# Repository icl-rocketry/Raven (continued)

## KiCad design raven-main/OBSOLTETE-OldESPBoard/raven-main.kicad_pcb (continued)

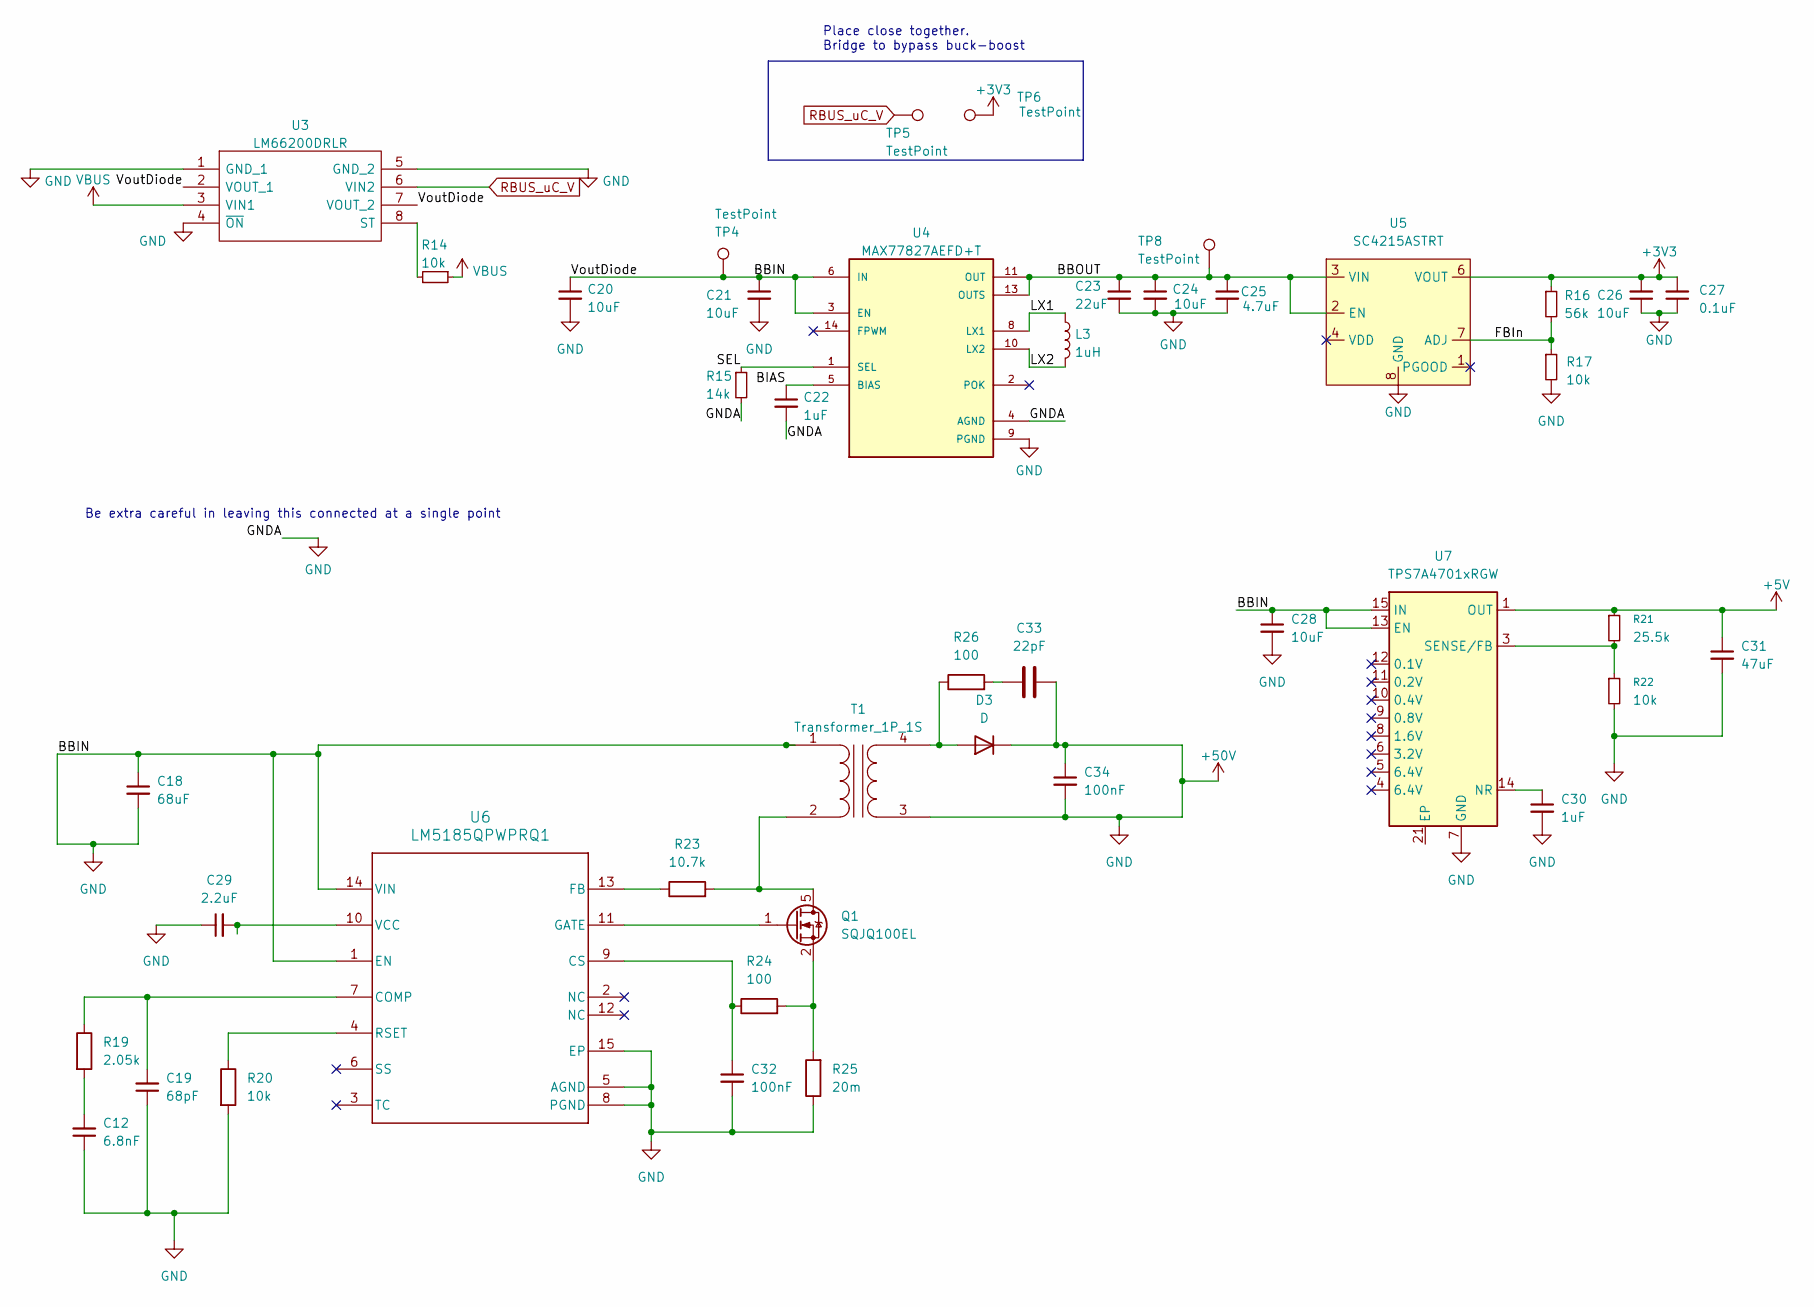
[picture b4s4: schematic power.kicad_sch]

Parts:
C12: 6.8nF; C_0402_1005Metric
C18: 68uF; C_0402_1005Metric
C19: 68pF; C_0402_1005Metric
C20, C24, C26, C28: 10uF; C_0402_1005Metric
C21: 10uF; C_0603_1608Metric
C22, C30: 1uF; C_0402_1005Metric
C23: 22uF; C_0603_1608Metric
C25: 4.7uF; C_0402_1005Metric
C27: 0.1uF; C_0402_1005Metric
C29: 2.2uF; C_0402_1005Metric
C31: 47uF; C_0402_1005Metric
C32, C34: 100nF; C_0402_1005Metric
C33: 22pF; C_0402_1005Metric
D3: D
L3: 1uH; L_0805_2012Metric
Q1: SQJQ100EL; LFPAK88
R14, R17, R20, R22: 10k; R_0402_1005Metric
R15: 14k; R_0402_1005Metric
R16: 56k; R_0402_1005Metric
R19: 2.05k; R_0402_1005Metric
R21: 25.5k; R_0402_1005Metric
R23: 10.7k; R_0402_1005Metric
R24, R26: 100; R_0402_1005Metric
R25: 20m; R_0402_1005Metric
T1: Transformer_1P_1S
TP4, TP5, TP6, TP8: TestPoint; TestPoint_Pad_D1.5mm
U3: LM66200DRLR; SOTFL50P160X60-8N; Manufacturer_Part_Number LM66200DRLR; Mouser Part Number 595-LM66200DRLR
U4: MAX77827AEFD+T; CONV_MAX77827AEFD+T; PARTREV B
U5: SC4215ASTRT; SOIC127P599X175-9N
U6: LM5185QPWPRQ1; PWP0014G-IPC_A
U7: TPS7A4701xRGW; Texas_RGW0020A_VQFN-20-1EP_5x5mm_P0.65mm_EP3.15x3.15mm_Ther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

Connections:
+3V3: C26.2, C27.2, R16.1, TP6.1 (1_1), U5.6 (VOUT); also elsewhere on the board
+5V: C31.1, R21.1, U7.1 (OUT), U7.20 (OUT); also elsewhere on the board
+50V: C12.1, C18.1, C18.2, C19.1, C20.1, C20.2, C21.1, C21.2, C22.2, C23.2, C24.2, C25.2, C26.1, C27.1, C28.1, C28.2, C29.1, C30.2, C31.2, C32.2, C33.2, C34.1, C34.2, D3.1 (K), R15.2, R17.2, R20.2, R22.2, R25.1, T1.1 (AA), T1.3 (SA), TP4.1 (1_1), U3.1 (GND_1), U3.2 (VOUT_1), U3.4 (~ON), U3.5 (GND_2), U3.7 (VOUT_2), U4.3 (EN), U4.4 (AGND), U4.6 (IN), U4.9 (PGND), U5.8 (GND), U5.9 (GND), U6.1 (EN), U6.5 (AGND), U6.8 (PGND), U6.14 (VIN), U6.15 (EP), U7.7 (GND), U7.13 (EN), U7.15 (IN), U7.16 (IN); also elsewhere on the board
/Power/BBOUT: C23.1, C24.1, C25.1, TP8.1 (1_1), U4.11 (OUT), U4.13 (OUTS), U5.2 (EN), U5.3 (VIN)
/Power/BIAS: C22.1, U4.5 (BIAS)
/Power/FBIn: R16.2, R17.1, U5.7 (ADJ)
/Power/LX1: L3.1, U4.8 (LX1)
/Power/LX2: L3.2, U4.10 (LX2)
/Power/SEL: R15.1, U4.1 (SEL)
unnamed: C12.2, R19.2
unnamed: C33.1, R26.2
unnamed: D3.2 (A), R26.1, T1.4 (SB)
unnamed: Q1.5 (D), R23.2, T1.2 (AB)
unnamed: Q1.1 (G), U6.11 (GATE)
unnamed: Q1.2 (S), Q1.3 (S), Q1.4 (S), R24.2, R25.2
unnamed: R14.2, U3.8 (ST)
unnamed: C19.2, R19.1, U6.7 (COMP)
unnamed: C32.1, R24.1, U6.9 (CS)
unnamed: R23.1, U6.13 (FB)
unnamed: R20.1, U6.4 (RSET)
unnamed: C29.2, U6.10 (VCC)
unnamed: C30.1, U7.14 (NR)
unnamed: R21.2, R22.1, U7.3 (SENSE/FB)
RBUS_uC_V: TP5.1 (1_1), U3.6 (VIN2); also elsewhere on the board
VBUS: R14.1, U3.3 (VIN1); also elsewhere on the board

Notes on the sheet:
Place close together. Bridge to bypass buck-boost
Be extra careful in leaving this connected at a single point

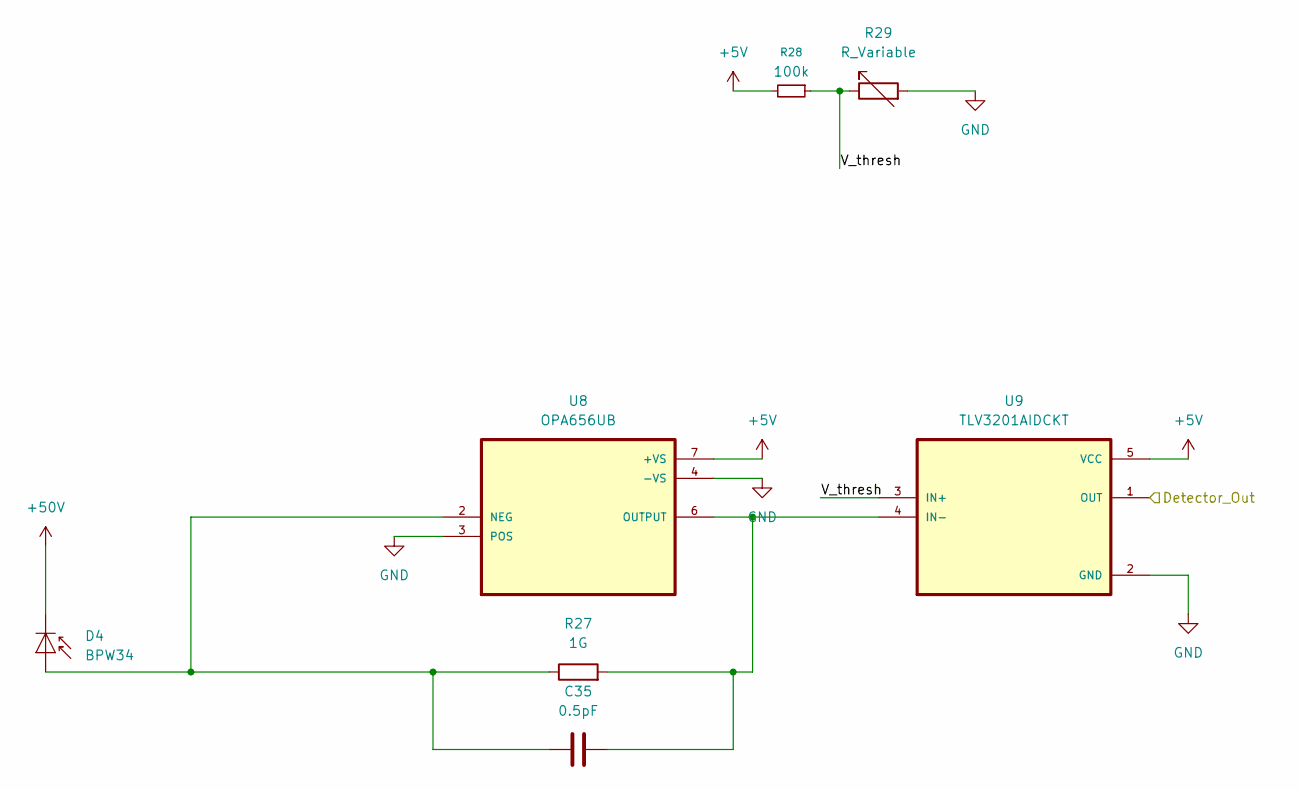
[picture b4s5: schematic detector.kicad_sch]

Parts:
C35: 0.5pF; C_0402_1005Metric
D4: BPW34; Osram_DIL2_4.3x4.65mm_P5.08mm
R27: 1G; R_0402_1005Metric
R28: 100k; R_0402_1005Metric
R29: R_Variable; R_0402_1005Metric
U8: OPA656UB; SOIC127P599X175-8N
U9: TLV3201AIDCKT; SOT65P210X110-5N

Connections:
+5V: R28.2, U8.7 (+VS), U9.5 (VCC); also elsewhere on the board
/detector/V_thresh_A: R28.1, R29.1, U9.3 (IN+)
unnamed: C35.1, D4.2 (A), R27.1, U8.2 (NEG)
unnamed: C35.2, R27.2, U8.6 (OUTPUT), U9.4 (IN-)
unnamed 49: R29.2, U8.3 (POS), U8.4 (-VS), U9.2 (GND); also elsewhere on the board

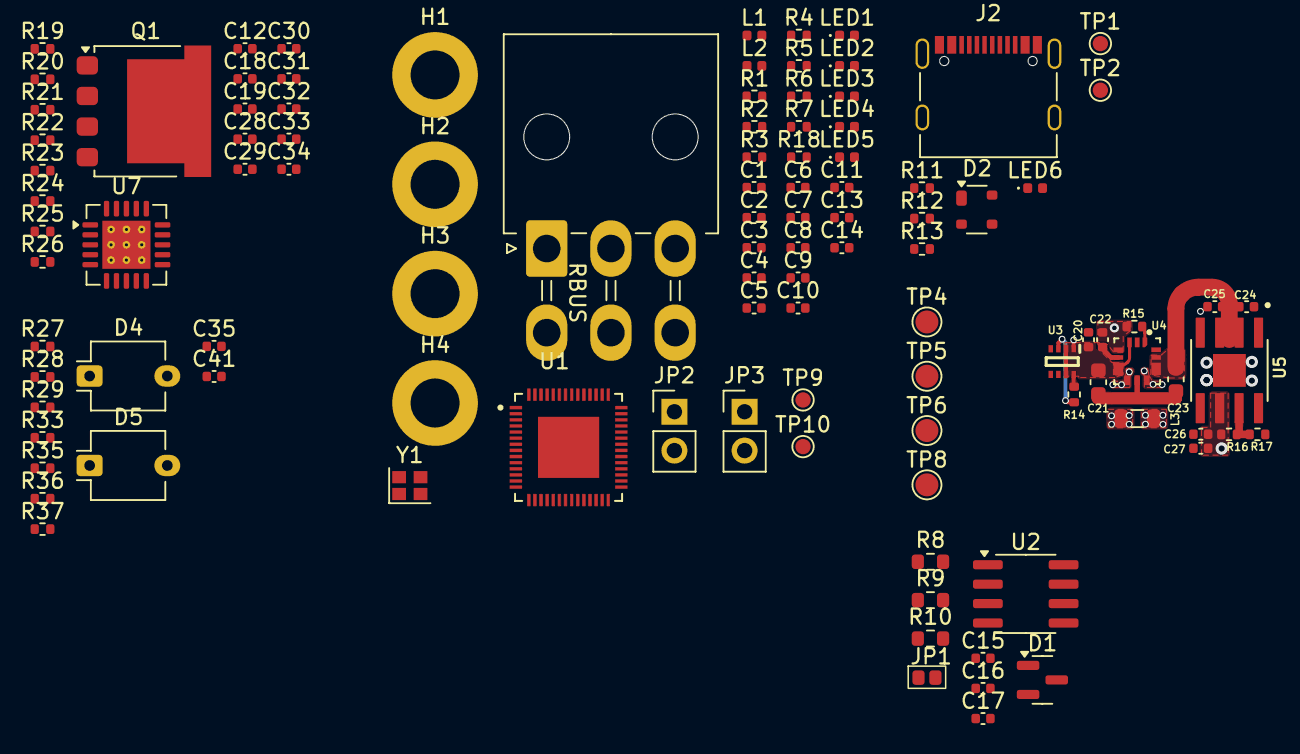
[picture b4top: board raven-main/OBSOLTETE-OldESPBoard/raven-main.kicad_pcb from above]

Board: 4 copper layers, 107 parts (0 on the bottom side), 53 nets.

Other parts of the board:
C41: 0.5pF; C_0402_1005Metric
D5: BPW34; Osram_DIL2_4.3x4.65mm_P5.08mm
R33: 1G; R_0402_1005Metric
R35: 100k; R_0402_1005Metric
R36: R_Variable; R_0402_1005Metric
R37: 200; R_0402_1005Metric

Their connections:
+5V: R35.2; also elsewhere on the board
+50V: R36.2, R37.1; also elsewhere on the board
/detector/V_thresh_B: R35.1, R36.1
unnamed: C41.1, D5.2 (A), R33.1
unnamed: C41.2, R33.2
unnamed 49: R37.2; also elsewhere on the board

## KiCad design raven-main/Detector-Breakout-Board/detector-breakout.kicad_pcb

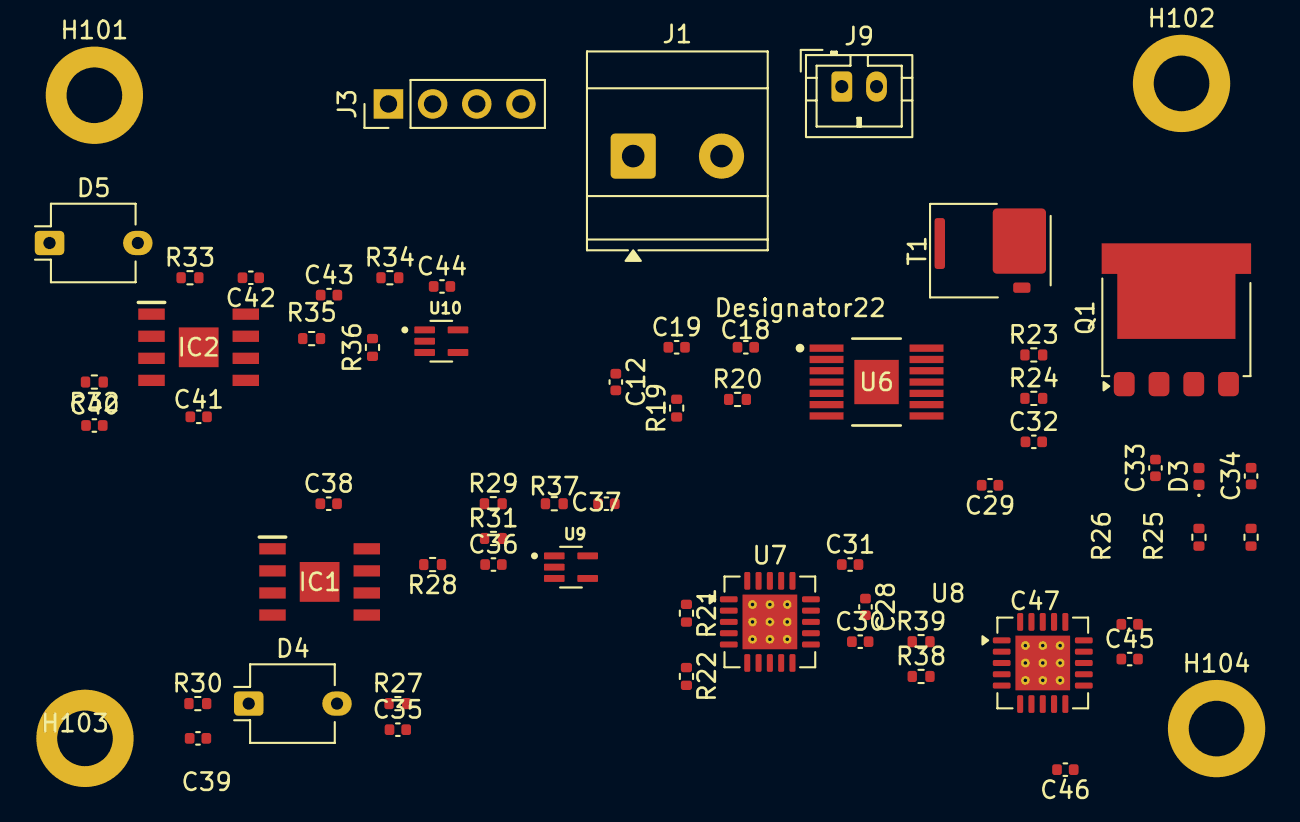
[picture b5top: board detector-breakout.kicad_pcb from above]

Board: 2 copper layers, 63 parts (0 on the bottom side), 29 nets, no tracks yet.

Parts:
C12: 6.8nF; C_0402_1005Metric
C18: 68uF; C_0402_1005Metric
C19: 68pF; C_0402_1005Metric
C28, C36, C43, C45: 10uF; C_0402_1005Metric
C29: 2.2uF; C_0402_1005Metric
C30, C46: 1uF; C_0402_1005Metric
C31, C47: 47uF; C_0402_1005Metric
C32, C34, C37, C38, C39, C40, C42, C44: 100nF; C_0402_1005Metric
C33: 22pF; C_0402_1005Metric
C35, C41: 0.5pF; C_0402_1005Metric
D3: D; D_0402_1005Metric
D4, D5: BPW34; Osram_DIL2_4.3x4.65mm_P5.08mm
H101, H102, H103, H104: MountingHole_Pad; MountingHole_3.2mm_M3_DIN965_Pad
IC1, IC2: ADA4817-1ARDZ-R7; SOIC127P600X175-9N
J1: DeployLipo; TerminalBlock_Phoenix_MKDS-3-2-5.08_1x02_P5.08mm_Horizontal
J3: Conn_01x04; PinHeader_1x04_P2.54mm_Vertical
J9: UCLipo; JST_PH_B2B-PH-K_1x02_P2.00mm_Vertical
Q1: SQJQ100EL; LFPAK88
R19: 2.05k; R_0402_1005Metric
R20: 10k; R_0402_1005Metric
R21: 25.5k; R_0402_1005Metric
R22, R39: 9.76k; R_0402_1005Metric
R23: 10.7k; R_0402_1005Metric
R24, R26: 100; R_0402_1005Metric
R25: 20m; R_0402_1005Metric
R27, R33: 1G; R_0402_1005Metric
R28, R35: 100k; R_0402_1005Metric
R29, R36: R_Variable; R_0402_1005Metric
R30, R32: 10K; R_0402_1005Metric
R31, R34: 1M; R_0402_1005Metric
R37: 200; R_0402_1005Metric
R38: 13.3k; R_0402_1005Metric
T1: Transformer_1P_1S; GaN_Systems_GaNPX-3_5x6.6mm_Drain2.93x0.6mm
U6: LM5185QPWPRQ1; PWP0014G-IPC_A
U7, U8: TPS7A4701xRGW; Texas_RGW0020A_VQFN-20-1EP_5x5mm_P0.65mm_EP3.15x3.15mm_Ther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
U9, U10: TLV3201AIDCKT; SOT65P210X110-5N

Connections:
+3V3: C37.2, C44.2, C47.1, R38.1, U8.1 (OUT), U8.20 (OUT), U9.5 (VCC), U10.5 (VCC)
+5V: C31.1, C36.1, C38.2, C42.2, C43.1, IC1.7 (+VS), IC1.8 (~PD), IC2.7 (+VS), IC2.8 (~PD), R21.1, R28.2, R35.2, U7.1 (OUT), U7.20 (OUT)
+50V: C12.1, C18.1, C18.2, C19.1, C28.1, C28.2, C29.1, C30.2, C31.2, C32.2, C33.2, C34.1, C34.2, C36.2, C37.1, C38.1, C39.2, C40.2, C42.1, C43.2, C44.1, C45.1, C45.2, C46.2, C47.2, D3.1 (K), H101.1 (1_1), H102.1 (1_1), H103.1 (1_1), H104.1 (1_1), IC1.3 (+IN), IC1.4 (-VS), IC1.9 (EP), IC2.3 (+IN), IC2.4 (-VS), IC2.9 (EP), J1.1, J1.2, J3.3, J9.1, J9.2, R20.2, R22.2, R25.1, R30.1, R32.1, R36.2, R37.1, R39.2, T1.1 (AA), T1.3 (SA), U6.1 (EN), U6.5 (AGND), U6.8 (PGND), U6.14 (VIN), U6.15 (EP), U7.7 (GND), U7.13 (EN), U7.15 (IN), U7.16 (IN), U8.7 (GND), U8.13 (EN), U8.15 (IN), U8.16 (IN), U9.2 (GND), U10.2 (GND)
/detector/Detector_Out_A: J3.1, R31.2, U9.1 (OUT)
/detector/Detector_Out_B: J3.2, R34.2, U10.1 (OUT)
/detector/V_thresh_A: R28.1, R29.1, R31.1, U9.3 (IN+)
/detector/V_thresh_B: R34.1, R35.1, R36.1, U10.3 (IN+)
unnamed: C12.2, R19.2
unnamed: C33.1, R26.2
unnamed: D3.2 (A), R26.1
unnamed: C35.1, D4.2 (A), IC1.2 (-IN), R27.1
unnamed: C39.1, D4.1 (K), R30.2
unnamed: C41.1, D5.2 (A), IC2.2 (-IN), R33.1
unnamed: C40.1, D5.1 (K), R32.2
unnamed: C35.2, IC1.6 (OUT), R27.2, U9.4 (IN-)
unnamed: C41.2, IC2.6 (OUT), R33.2, U10.4 (IN-)
unnamed: Q1.5 (D), R23.2, T1.2 (AB)
unnamed: Q1.1 (G), U6.11 (GATE)
unnamed: Q1.2 (S), Q1.3 (S), Q1.4 (S), R24.2, R25.2
unnamed: R29.2, R37.2
unnamed: C19.2, R19.1, U6.7 (COMP)
unnamed: C32.1, R24.1, U6.9 (CS)
unnamed: R23.1, U6.13 (FB)
unnamed: R20.1, U6.4 (RSET)
unnamed: C29.2, U6.10 (VCC)
unnamed: C30.1, U7.14 (NR)
unnamed: R21.2, R22.1, U7.3 (SENSE/FB)
unnamed: C46.1, U8.14 (NR)
unnamed: R38.2, R39.1, U8.3 (SENSE/FB)

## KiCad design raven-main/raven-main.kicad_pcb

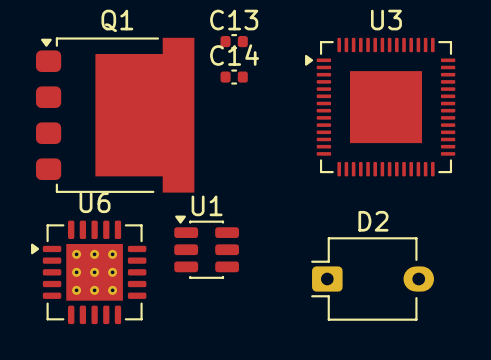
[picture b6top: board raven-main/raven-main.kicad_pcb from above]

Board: 2 copper layers, 7 parts (0 on the bottom side), 5 nets, no tracks yet.

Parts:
C13: 10uF; C_0402_1005Metric
C14: 22uF; C_0402_1005Metric
D2: BPW34; Osram_DIL2_4.3x4.65mm_P5.08mm
Q1: SQJQ100EL; LFPAK88
U1: TPS563200; SOT-23-6
U3: ESP32-S3; QFN-56-1EP_7x7mm_P0.4mm_EP4x4mm
U6: TPS7A4701xRGW; Texas_RGW0020A_VQFN-20-1EP_5x5mm_P0.65mm_EP3.15x3.15mm_Ther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

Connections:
/3.3V: C14.1, U3.55 (VDDA), U3.56 (VDDA)
/5V: U6.1 (OUT), U6.20 (OUT)
GND: C13.1, C13.2, C14.2, D2.1 (K), U1.1 (GND), U1.3 (VIN), U1.5 (EN), U3.57 (GND), U6.7 (GND), U6.13 (EN), U6.15 (IN), U6.16 (IN)
unnamed: Q1.2 (S), Q1.3 (S), Q1.4 (S)
unnamed: U3.2 (VDD3P3), U3.3 (VDD3P3)

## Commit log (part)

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2026-06-16 Initialised Repo
2026-06-16 Created detector circuit
2026-06-16 Added opamp circuits
2026-06-16 Added Readme
2026-06-16 Added LDO Regulator
2026-06-17 Forgot the changes lol
2026-06-17 Used the ESP-32 board template to create full board
